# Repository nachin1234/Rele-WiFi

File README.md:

Este proyecto consiste en el desarrollo de un relé WiFi controlado mediante un ESP8266, cuyo objetivo principal es permitir el accionamiento remoto de una alarma o timbre utilizando una conexión WiFi.

El sistema permite enviar una señal desde un dispositivo conectado a la misma red, como una computadora o un teléfono celular, para activar o desactivar el relé. De esta manera, se puede controlar un dispositivo eléctrico de forma inalámbrica, evitando la necesidad de utilizar un interruptor físico conectado directamente al sistema.

Integrantes: Soria Ignacio y Sachetti Thomas

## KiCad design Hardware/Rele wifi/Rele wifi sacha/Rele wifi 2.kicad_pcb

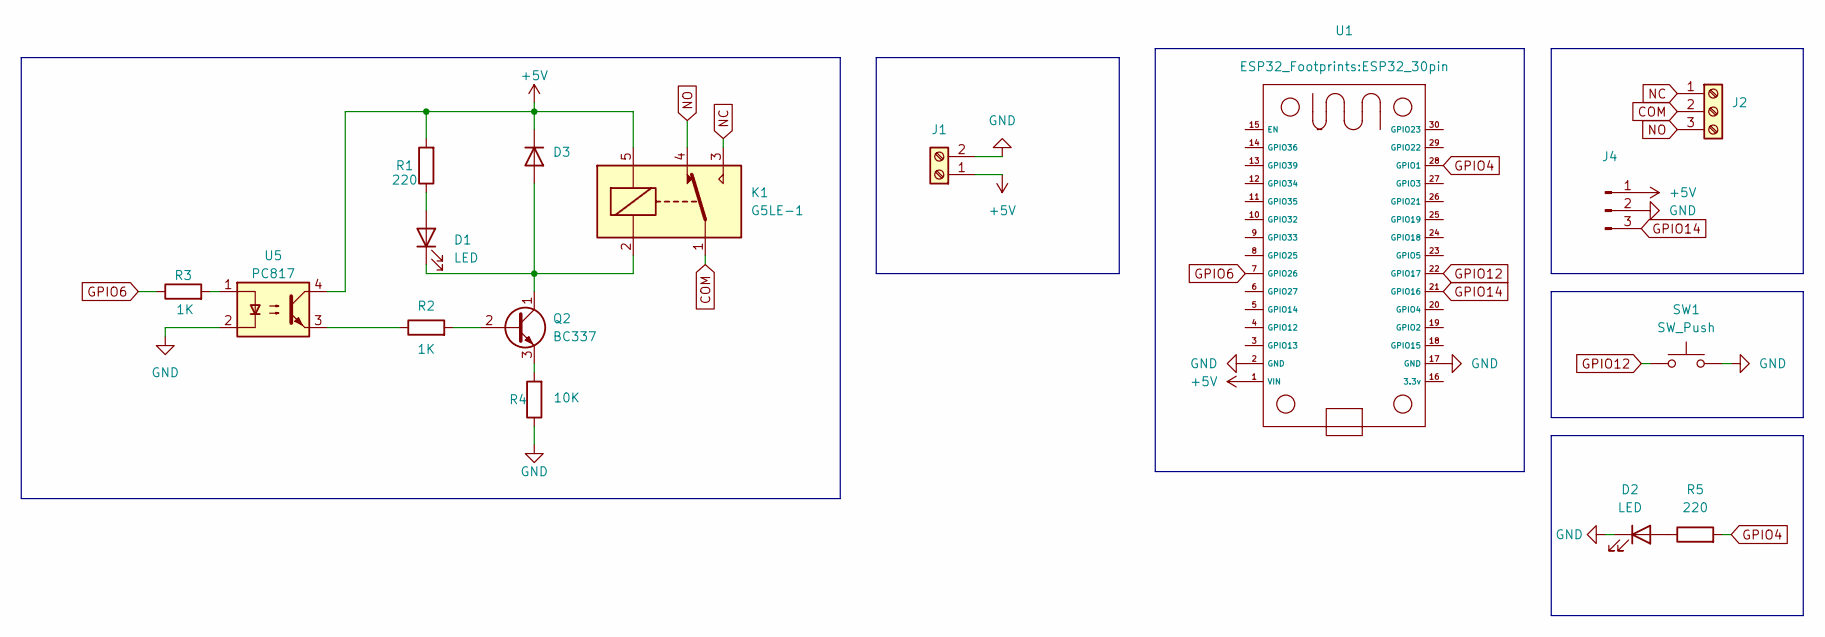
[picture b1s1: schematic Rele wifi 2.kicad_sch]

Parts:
D1, D2: LED; LED_D3.0mm_Clear
D3: 1N4007; D_DO-41_SOD81_P12.70mm_Horizontal
J1: Screw_Terminal_01x02; TerminalBlock_Phoenix_MKDS-1,5-2-5.08_1x02_P5.08mm_Horizont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
J2: Screw_Terminal_01x03; TerminalBlock_Phoenix_MKDS-1,5-3-5.08_1x03_P5.08mm_Horizont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
J4: Conn_01x03_Pin; PinSocket_1x03_P2.54mm_Vertical
K1: G5LE-1; Relay_SPDT_Omron-G5LE-1
Q2: BC337; TO-92_Inline
R1, R5: 220; R_0805_2012Metric
R2, R3: 1K; R_0805_2012Metric
R4: 10K; R_0805_2012Metric
SW1: SW_Push; SW_PUSH_1P1T_6x3.5mm_H5.0_APEM_MJTP1250
U1: ESP32_30pin
U5: PC817; SOP-4_7.5x4.1mm_P2.54mm

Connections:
+5V: D3.1 (K), J1.1, J4.1, K1.5, R1.2, U1.1 (VIN), U5.4
COM: J2.2, K1.1
GND: D2.1 (K), J1.2, J4.2, R4.1, SW1.2, U1.2 (GND), U1.17 (GND), U5.2
GPIO4: R5.2, U1.28 (GPIO1)
GPIO6: R3.1, U1.7 (GPIO26)
GPIO12: SW1.1, U1.22 (GPIO17)
GPIO14: J4.3, U1.21 (GPIO16)
NC: J2.1, K1.3
NO: J2.3, K1.4
unnamed: D1.2 (A), R1.1
unnamed: D1.1 (K), D3.2 (A), K1.2, Q2.1 (C)
unnamed: D2.2 (A), R5.1
unnamed: Q2.2 (B), R2.2
unnamed: Q2.3 (E), R4.2
unnamed: R2.1, U5.3
unnamed: R3.2, U5.1

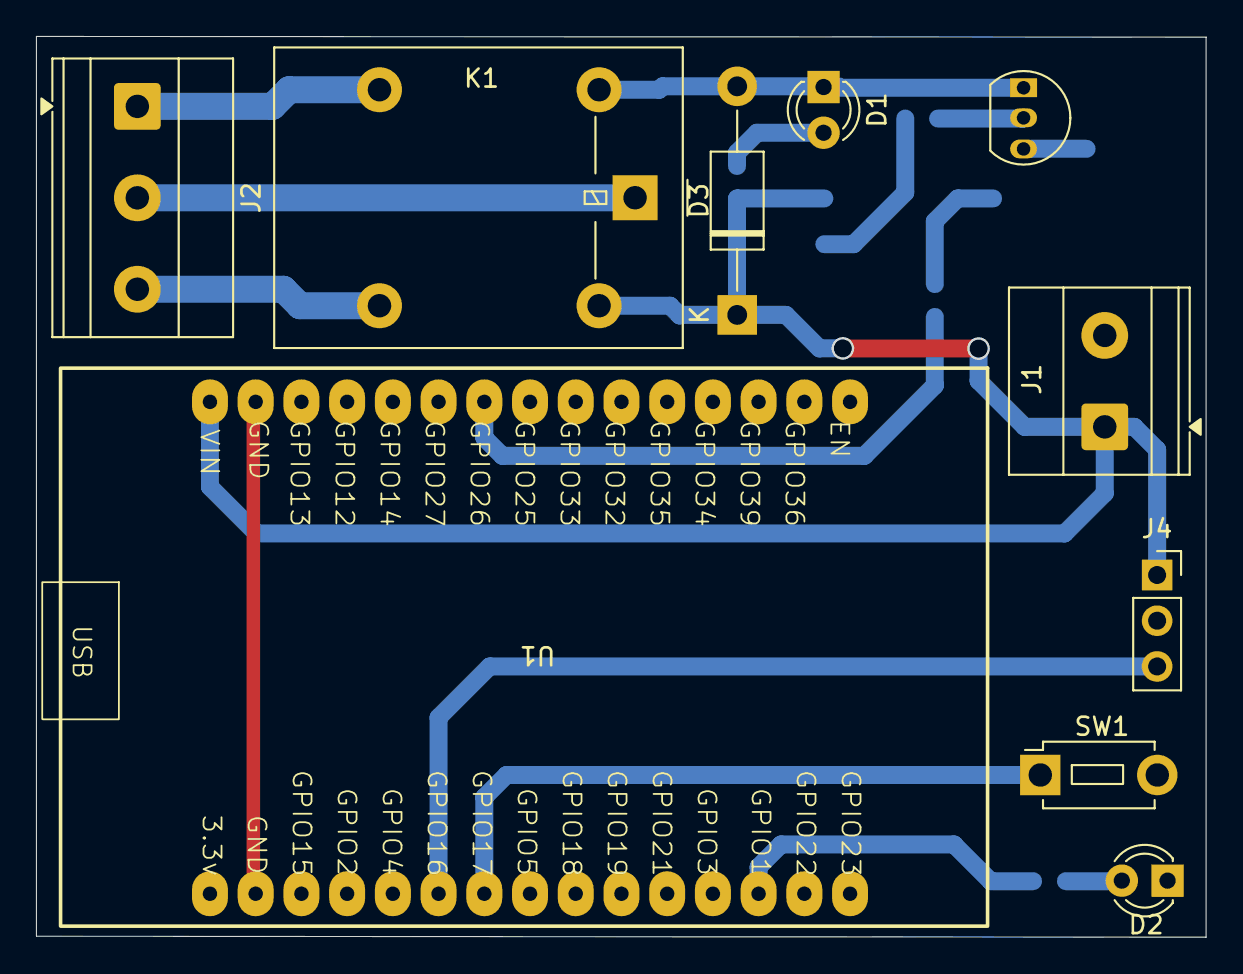
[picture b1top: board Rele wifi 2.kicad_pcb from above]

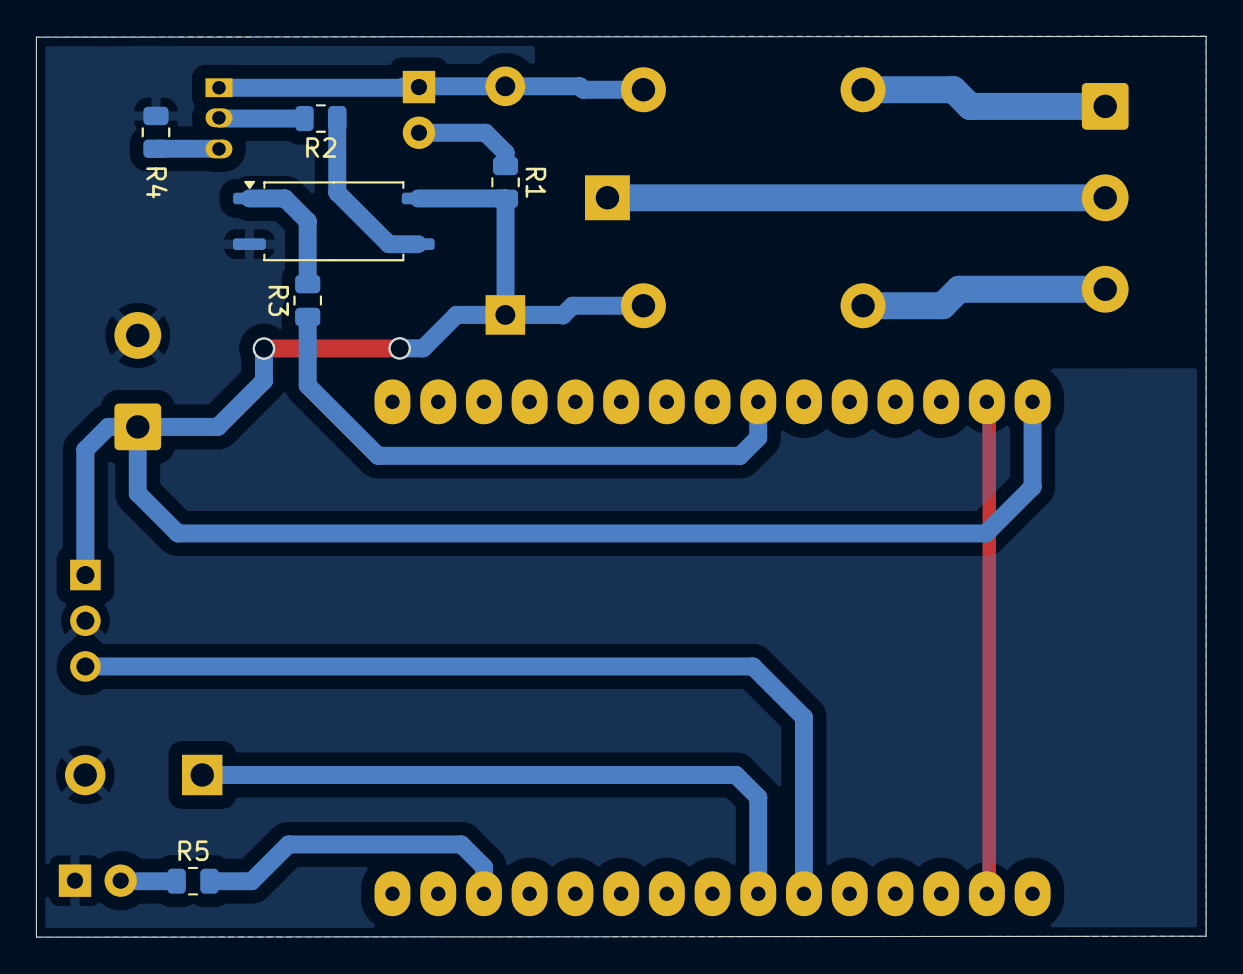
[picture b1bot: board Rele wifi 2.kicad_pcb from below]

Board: 2 copper layers, 65.0 x 50.0 mm, 16 parts (6 on the bottom side), 16 nets.

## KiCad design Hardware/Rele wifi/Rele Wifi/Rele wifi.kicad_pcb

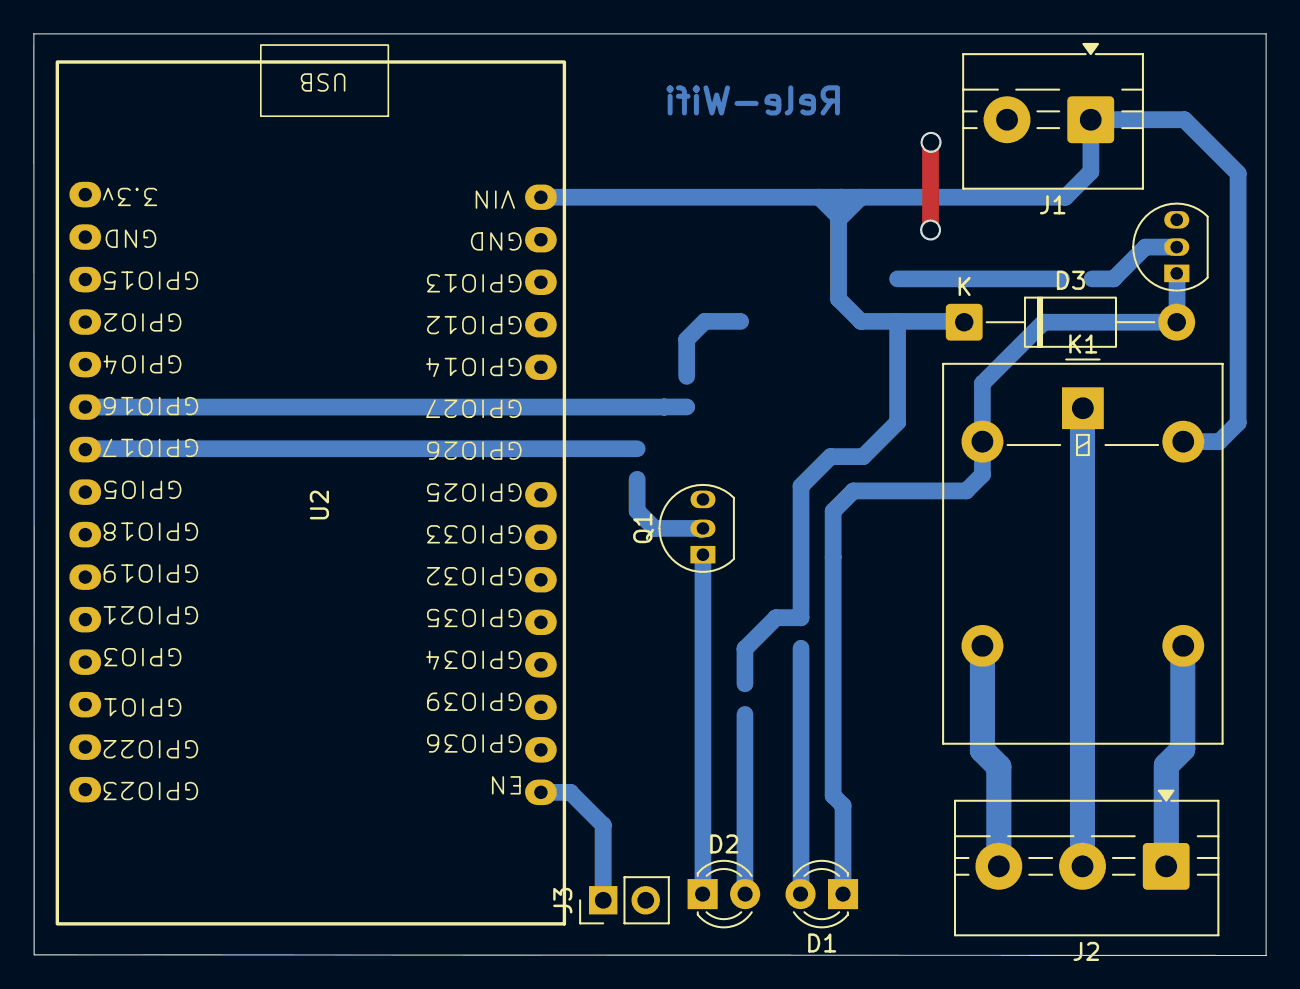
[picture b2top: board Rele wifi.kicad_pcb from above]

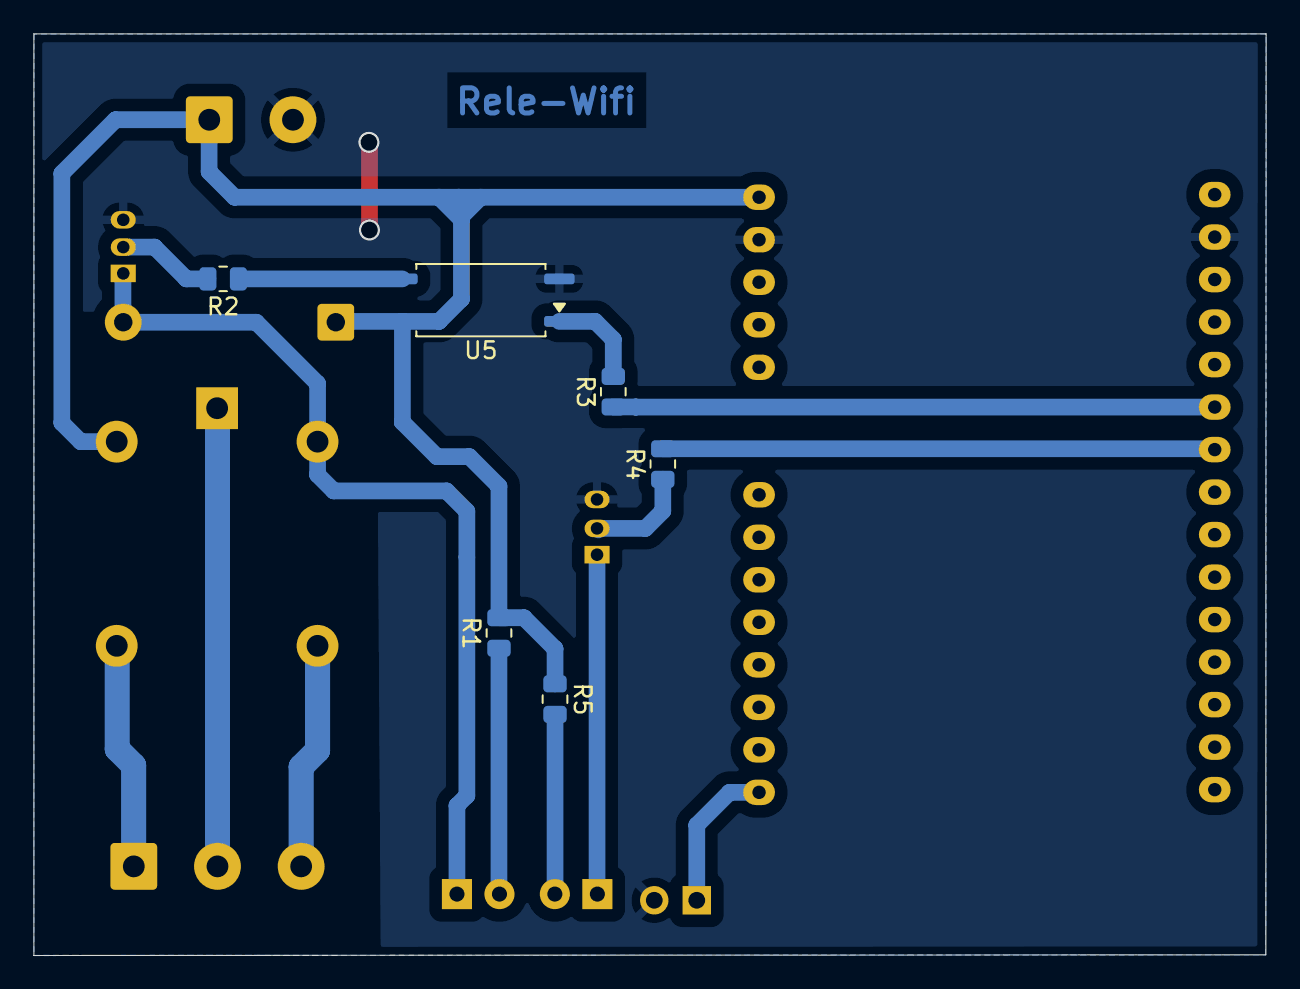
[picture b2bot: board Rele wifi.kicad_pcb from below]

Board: 2 copper layers, 73.6 x 55.1 mm, 16 parts (6 on the bottom side), 16 nets.

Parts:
D1: LED; LED_D3.0mm_Clear
D2: LED IR; LED_D3.0mm_Clear
D3: 1N4007; D_DO-41_SOD81_P12.70mm_Horizontal
J1: Screw_Terminal_01x02; TerminalBlock_MaiXu_MX126-5.0-02P_1x02_P5.00mm
J2: Screw_Terminal_01x03; TerminalBlock_MaiXu_MX126-5.0-03P_1x03_P5.00mm
J3: Conn_01x02_Pin; PinHeader_1x02_P2.54mm_Vertical
K1: G5LE-1; Relay_SPDT_Omron-G5LE-1
Q1, Q2: BC337; TO-92_Inline
R1, R4: 220; R_0805_2012Metric
R2, R3: 1K; R_0805_2012Metric
R5: 47; R_0805_2012Metric
U2: ESP32_30pin
U5: PC817; SOP-4_7.5x4.1mm_P2.54mm

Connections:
+5V: D3.1 (K), J1.1, K1.5, R1.2, R5.1, U2.1 (VIN), U5.4
COM: J2.2, K1.1
GND: J1.2, J3.2, Q1.3 (E), Q2.3 (E), U2.2 (GND), U2.17 (GND), U5.2
GPIO12: R3.1, U2.21 (GPIO16)
GPIO13: R4.2, U2.22 (GPIO17)
NC: J2.3, K1.3
NO: J2.1, K1.4
unnamed: D1.2 (A), R1.1
unnamed: D1.1 (K), D3.2 (A), K1.2, Q2.1 (C)
unnamed: D2.2 (A), R5.2
unnamed: D2.1 (K), Q1.1 (C)
unnamed: J3.1, U2.15 (EN)
unnamed: Q1.2 (B), R4.1
unnamed: Q2.2 (B), R2.2
unnamed: R2.1, U5.3
unnamed: R3.2, U5.1
